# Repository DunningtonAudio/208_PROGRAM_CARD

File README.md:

# 208_PROGRAM_CARD
A 208 program card project

These Model 208 Program Cards are designed to interface with the “PROGRAM BOARD” edge connector of a Buchla & Associates Model 208 Stored Program Sound Source module and its reissues / compatible units. Two versions are provided, one for standard use and one with a prototyping area where additional active circuitry can be added if desired. For guidance on general use, see Allen Strange’s “Programming and Meta-Programming the Electro Organism” manual.

Beyond the settings / connections available on the original cards, the following features are provided:

* A label area on the rear of the card for easy identification of presets.
* Modulation oscillator range switch setting (where this is available on the 208 edge connector).
* An extra connection point for each of the random voltage outputs.
* Footprints for optional multi-turn trimmer potentiometers (Bourns 3266W type) in series with the sequencer voltage level settings for fine tune when programming pitched sequences.
* 5V rail brought out to the prototyping area (where this is available on the 208 edge connector)

Please read the notes before ordering or using cards.

The repository contains:

* KiCad project files, including gerber outputs
* Schematic, notes and 208 manual as PDF files

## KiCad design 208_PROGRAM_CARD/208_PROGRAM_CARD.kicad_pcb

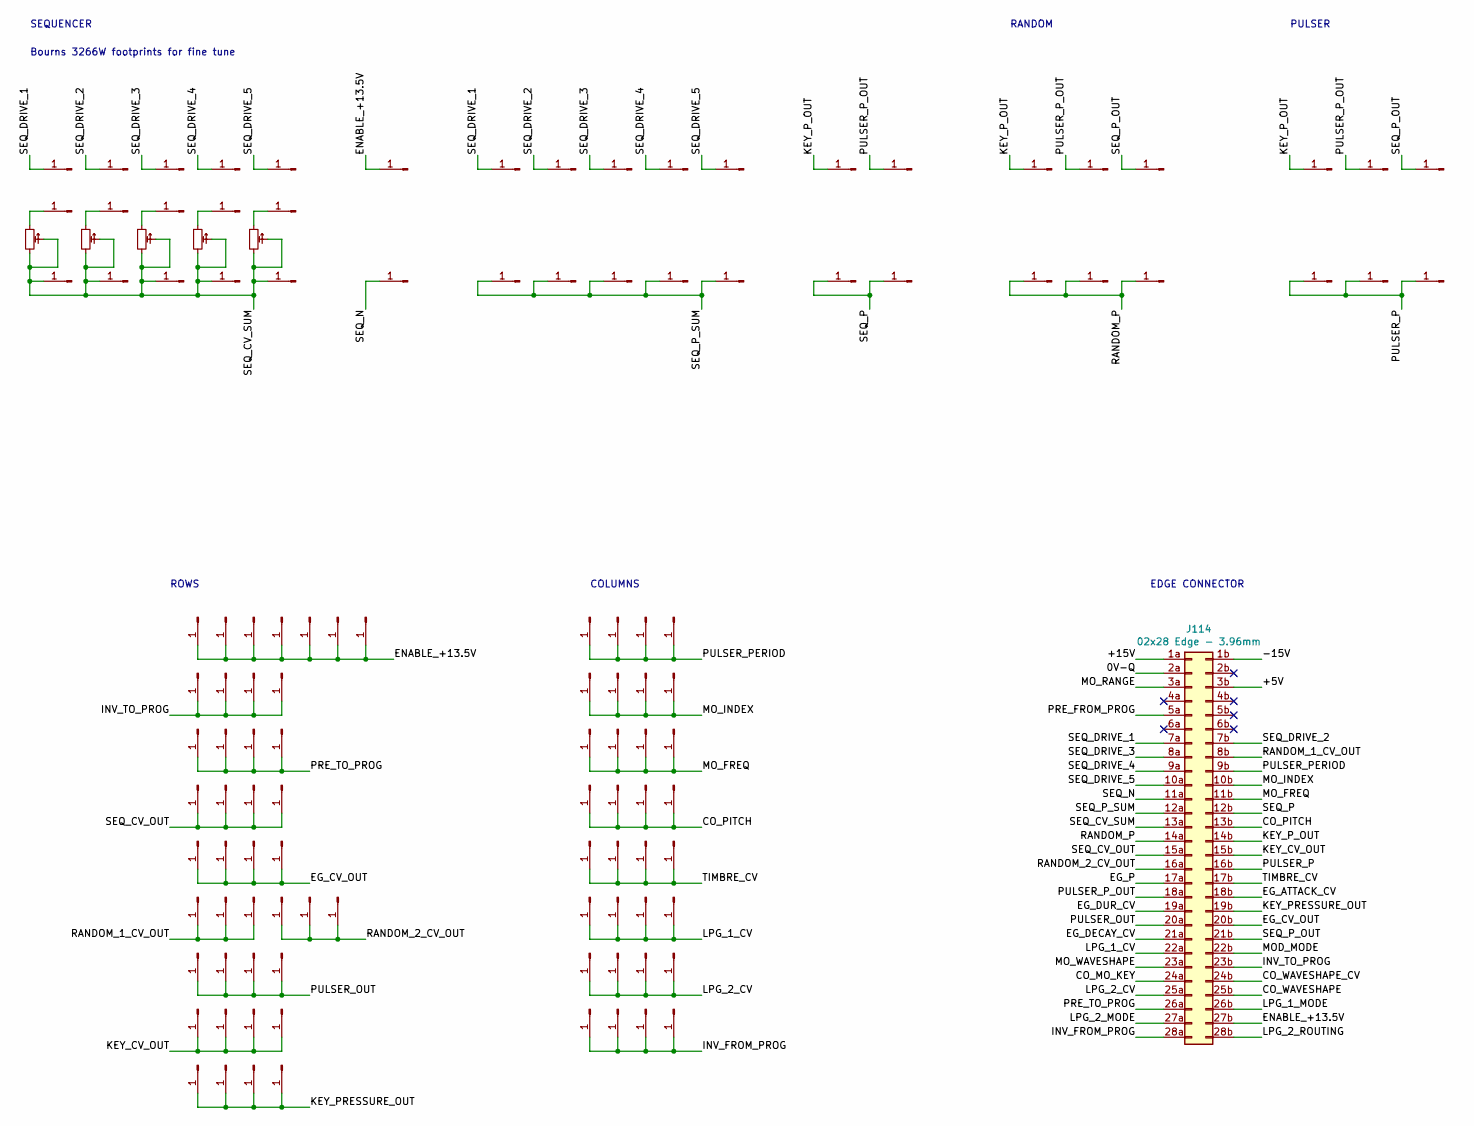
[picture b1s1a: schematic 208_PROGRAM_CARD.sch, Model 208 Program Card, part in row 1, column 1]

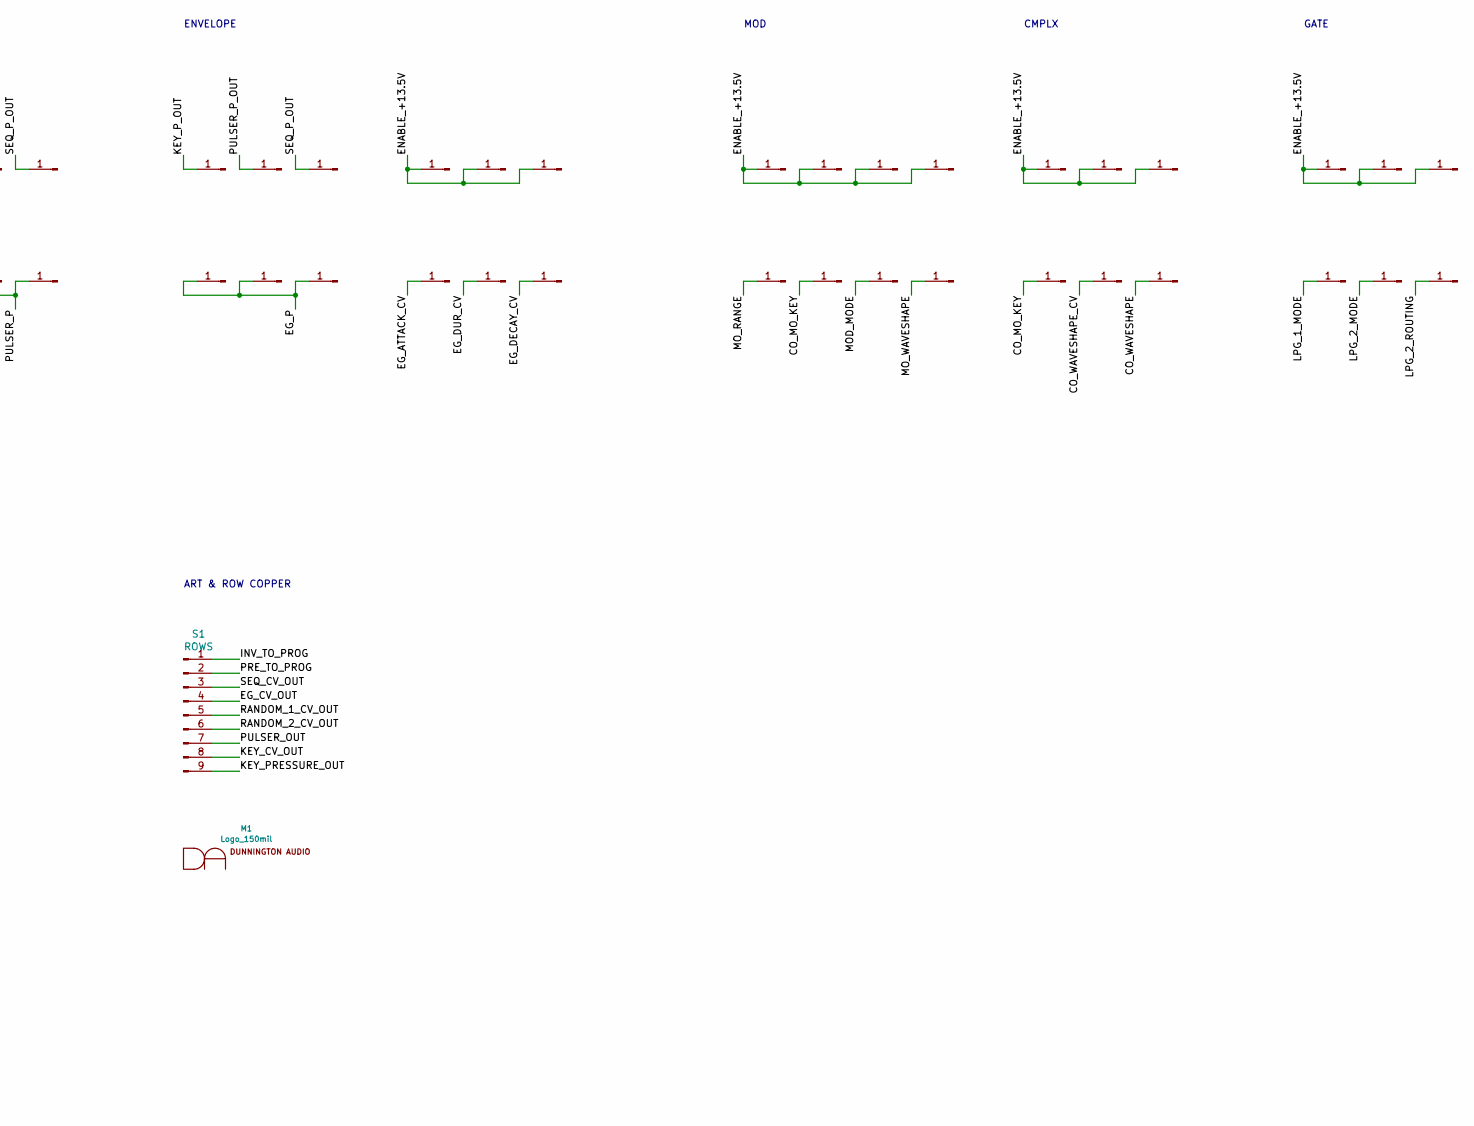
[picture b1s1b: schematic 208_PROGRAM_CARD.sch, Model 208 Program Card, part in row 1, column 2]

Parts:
J1, J2, J3, J4, J5, J6, J7, J8, J9, J10, J11, J12, J13, J14, J15, J16, J17, J18, J19, J20, J21, J22, J23, J24, J25, J26, J27, J28, J29, J30, J31, J32, J33, J34, J35, J36, J37, J38, J39, J40, J41, J42, J43, J44, J45, J46, J47, J48, J49, J50, J51, J52, J53, J54, J55, J56, J57, J58, J59, J60, J61, J62, J63, J64, J65, J66, J67, J68, J69, J70, J71, J72, J73, J74, J75, J76, J77, J78, J79, J80, J81, J82, J83, J84, J85, J86, J87, J88, J89, J90, J91, J92, J93, J94, J95, J96, J97, J98, J99, J100, J101, J102, J103, J104, J105, J106, J107, J108, J109, J110, J111, J112, J113, J115, J116, J117, J118, J119, J120, J121, J122, J123, J124, J125, J126, J127, J128, J129, J130, J131, J132, J133, J134, J135, J136, J137, J138, J139, J140, J141, J142, J143, J144, J354, J355, J356, J357, J358: Pad; SolderWirePad_1x01_Drill0.9mm
J114: 02x28 Edge - 3.96mm; 305-056-500-502_Mating_Edge
M1: Logo_150mil
S1: ROWS; 208_PROGRAM_CARD
TR1, TR2, TR3, TR4, TR5: TRIM; Potentiometer_Bourns_3266W_Vertical

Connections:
/0V-Q: J114.2a
/+5V: J114.3b
/+15V: J114.1a
/-15V: J114.1b
/CO_MO_KEY: J62.1, J65.1, J114.24a
/CO_PITCH: J102.1, J103.1, J104.1, J105.1, J114.13b
/CO_WAVESHAPE: J67.1, J114.25b
/CO_WAVESHAPE_CV: J66.1, J114.24b
/EG_ATTACK_CV: J58.1, J114.18b
/EG_CV_OUT: J106.1, J107.1, J108.1, J109.1, J114.20b, S1.4
/EG_DECAY_CV: J60.1, J114.21a
/EG_DUR_CV: J59.1, J114.19a
/EG_P: J55.1, J56.1, J57.1, J114.17a
/ENABLE_+13.5V: J6.1, J23.1, J24.1, J25.1, J26.1, J27.1, J28.1, J29.1, J30.1, J31.1, J32.1, J33.1, J34.1, J35.1, J71.1, J72.1, J73.1, J74.1, J75.1, J76.1, J77.1, J114.27b
/INV_FROM_PROG: J114.28a, J137.1, J138.1, J139.1, J140.1
/INV_TO_PROG: J82.1, J83.1, J84.1, J85.1, J114.23b, S1.1
/KEY_CV_OUT: J114.15b, J133.1, J134.1, J135.1, J136.1, S1.8
/KEY_PRESSURE_OUT: J114.19b, J141.1, J142.1, J143.1, J144.1, S1.9
/KEY_P_OUT: J12.1, J14.1, J17.1, J20.1, J114.14b
/LPG_1_CV: J114.22a, J121.1, J122.1, J123.1, J124.1
/LPG_1_MODE: J68.1, J114.26b
/LPG_2_CV: J114.25a, J129.1, J130.1, J131.1, J132.1
/LPG_2_MODE: J69.1, J114.27a
/LPG_2_ROUTING: J70.1, J114.28b
/MOD_MODE: J63.1, J114.22b
/MO_FREQ: J94.1, J95.1, J96.1, J97.1, J114.11b
/MO_INDEX: J86.1, J87.1, J88.1, J89.1, J114.10b
/MO_RANGE: J61.1, J114.3a
/MO_WAVESHAPE: J64.1, J114.23a
/PRE_FROM_PROG: J114.5a
/PRE_TO_PROG: J90.1, J91.1, J92.1, J93.1, J114.26a, S1.2
/PULSER_OUT: J114.20a, J125.1, J126.1, J127.1, J128.1, S1.7
/PULSER_P: J52.1, J53.1, J54.1, J114.16b
/PULSER_PERIOD: J78.1, J79.1, J80.1, J81.1, J114.9b
/PULSER_P_OUT: J13.1, J15.1, J18.1, J21.1, J114.18a
/RANDOM_1_CV_OUT: J114.8b, J115.1, J116.1, J117.1, S1.5
/RANDOM_2_CV_OUT: J114.16a, J118.1, J119.1, J120.1, S1.6
/RANDOM_P: J49.1, J50.1, J51.1, J114.14a
/SEQ_CV_OUT: J98.1, J99.1, J100.1, J101.1, J114.15a, S1.3
/SEQ_CV_SUM: J36.1, J37.1, J38.1, J39.1, J40.1, J114.13a, TR1.1, TR1.2, TR2.1, TR2.2, TR3.1, TR3.2, TR4.1, TR4.2, TR5.1, TR5.2
/SEQ_DRIVE_1: J1.1, J7.1, J114.7a
/SEQ_DRIVE_2: J2.1, J8.1, J114.7b
/SEQ_DRIVE_3: J3.1, J9.1, J114.8a
/SEQ_DRIVE_4: J4.1, J10.1, J114.9a
/SEQ_DRIVE_5: J5.1, J11.1, J114.10a
/SEQ_N: J41.1, J114.11a
/SEQ_P: J47.1, J48.1, J114.12b
/SEQ_P_OUT: J16.1, J19.1, J22.1, J114.21b
/SEQ_P_SUM: J42.1, J43.1, J44.1, J45.1, J46.1, J114.12a
/TIMBRE_CV: J110.1, J111.1, J112.1, J113.1, J114.17b
unnamed: J354.1, TR1.3
unnamed: J355.1, TR2.3
unnamed: J356.1, TR3.3
unnamed: J357.1, TR4.3
unnamed: J358.1, TR5.3

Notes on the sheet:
ROWS
COLUMNS
EDGE CONNECTOR
SEQUENCER
RANDOM
PULSER
ENVELOPE
MOD
CMPLX
GATE
ART & ROW COPPER
Bourns 3266W footprints for fine tune

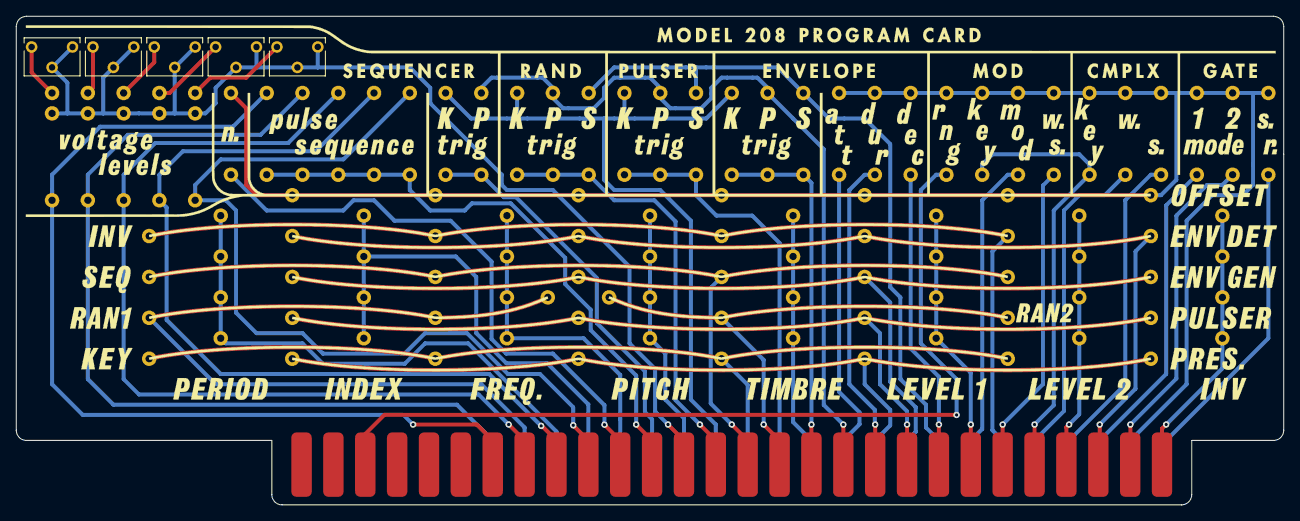
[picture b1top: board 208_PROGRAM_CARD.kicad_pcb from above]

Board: 2 copper layers, 157.5 x 60.7 mm, 156 parts (1 on the bottom side), 50 nets.

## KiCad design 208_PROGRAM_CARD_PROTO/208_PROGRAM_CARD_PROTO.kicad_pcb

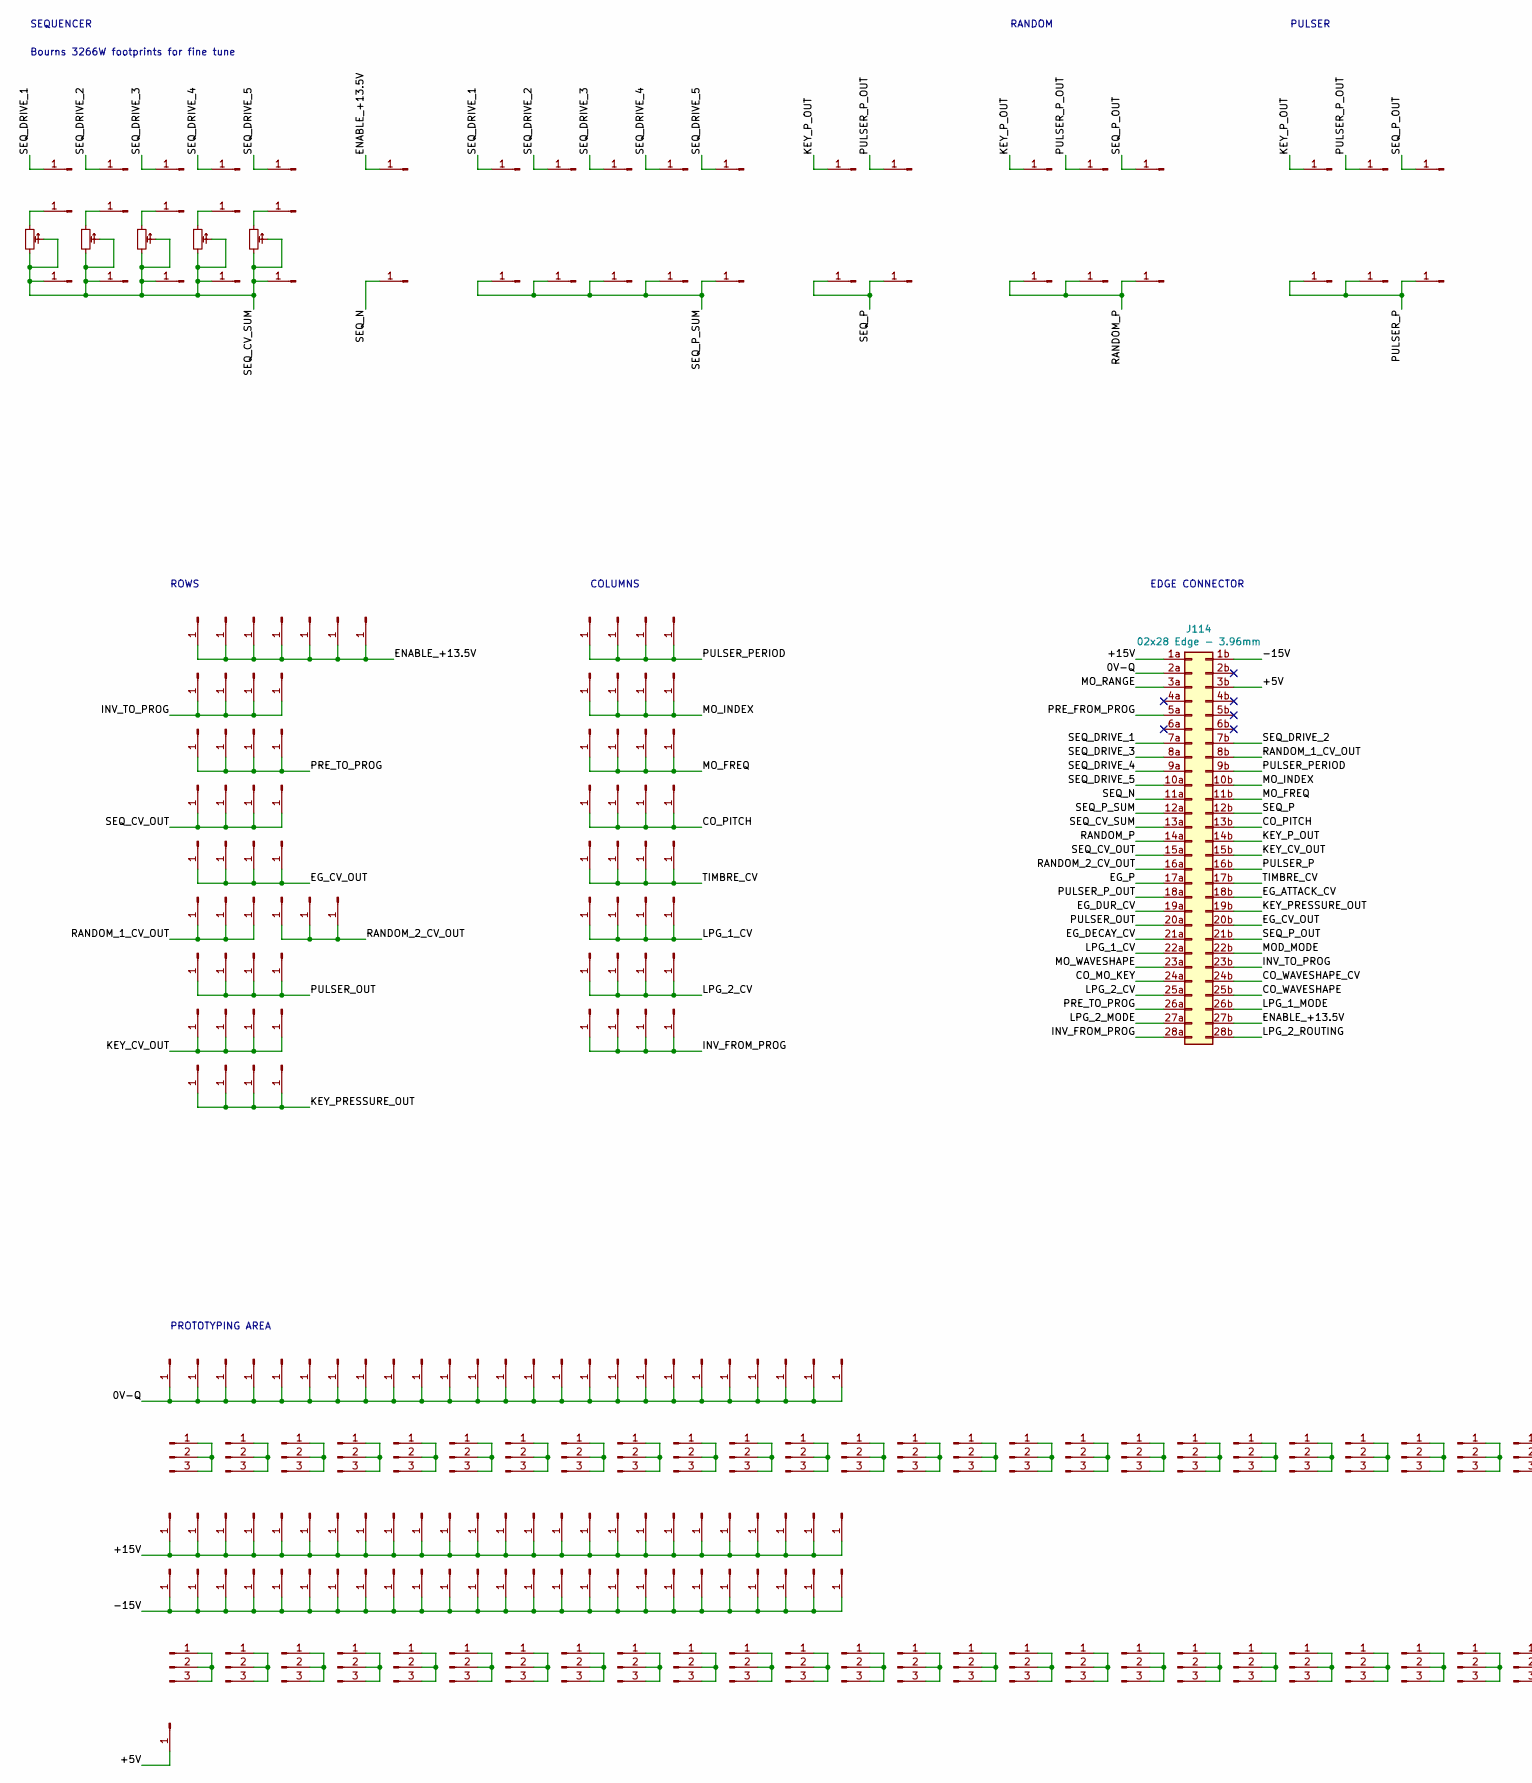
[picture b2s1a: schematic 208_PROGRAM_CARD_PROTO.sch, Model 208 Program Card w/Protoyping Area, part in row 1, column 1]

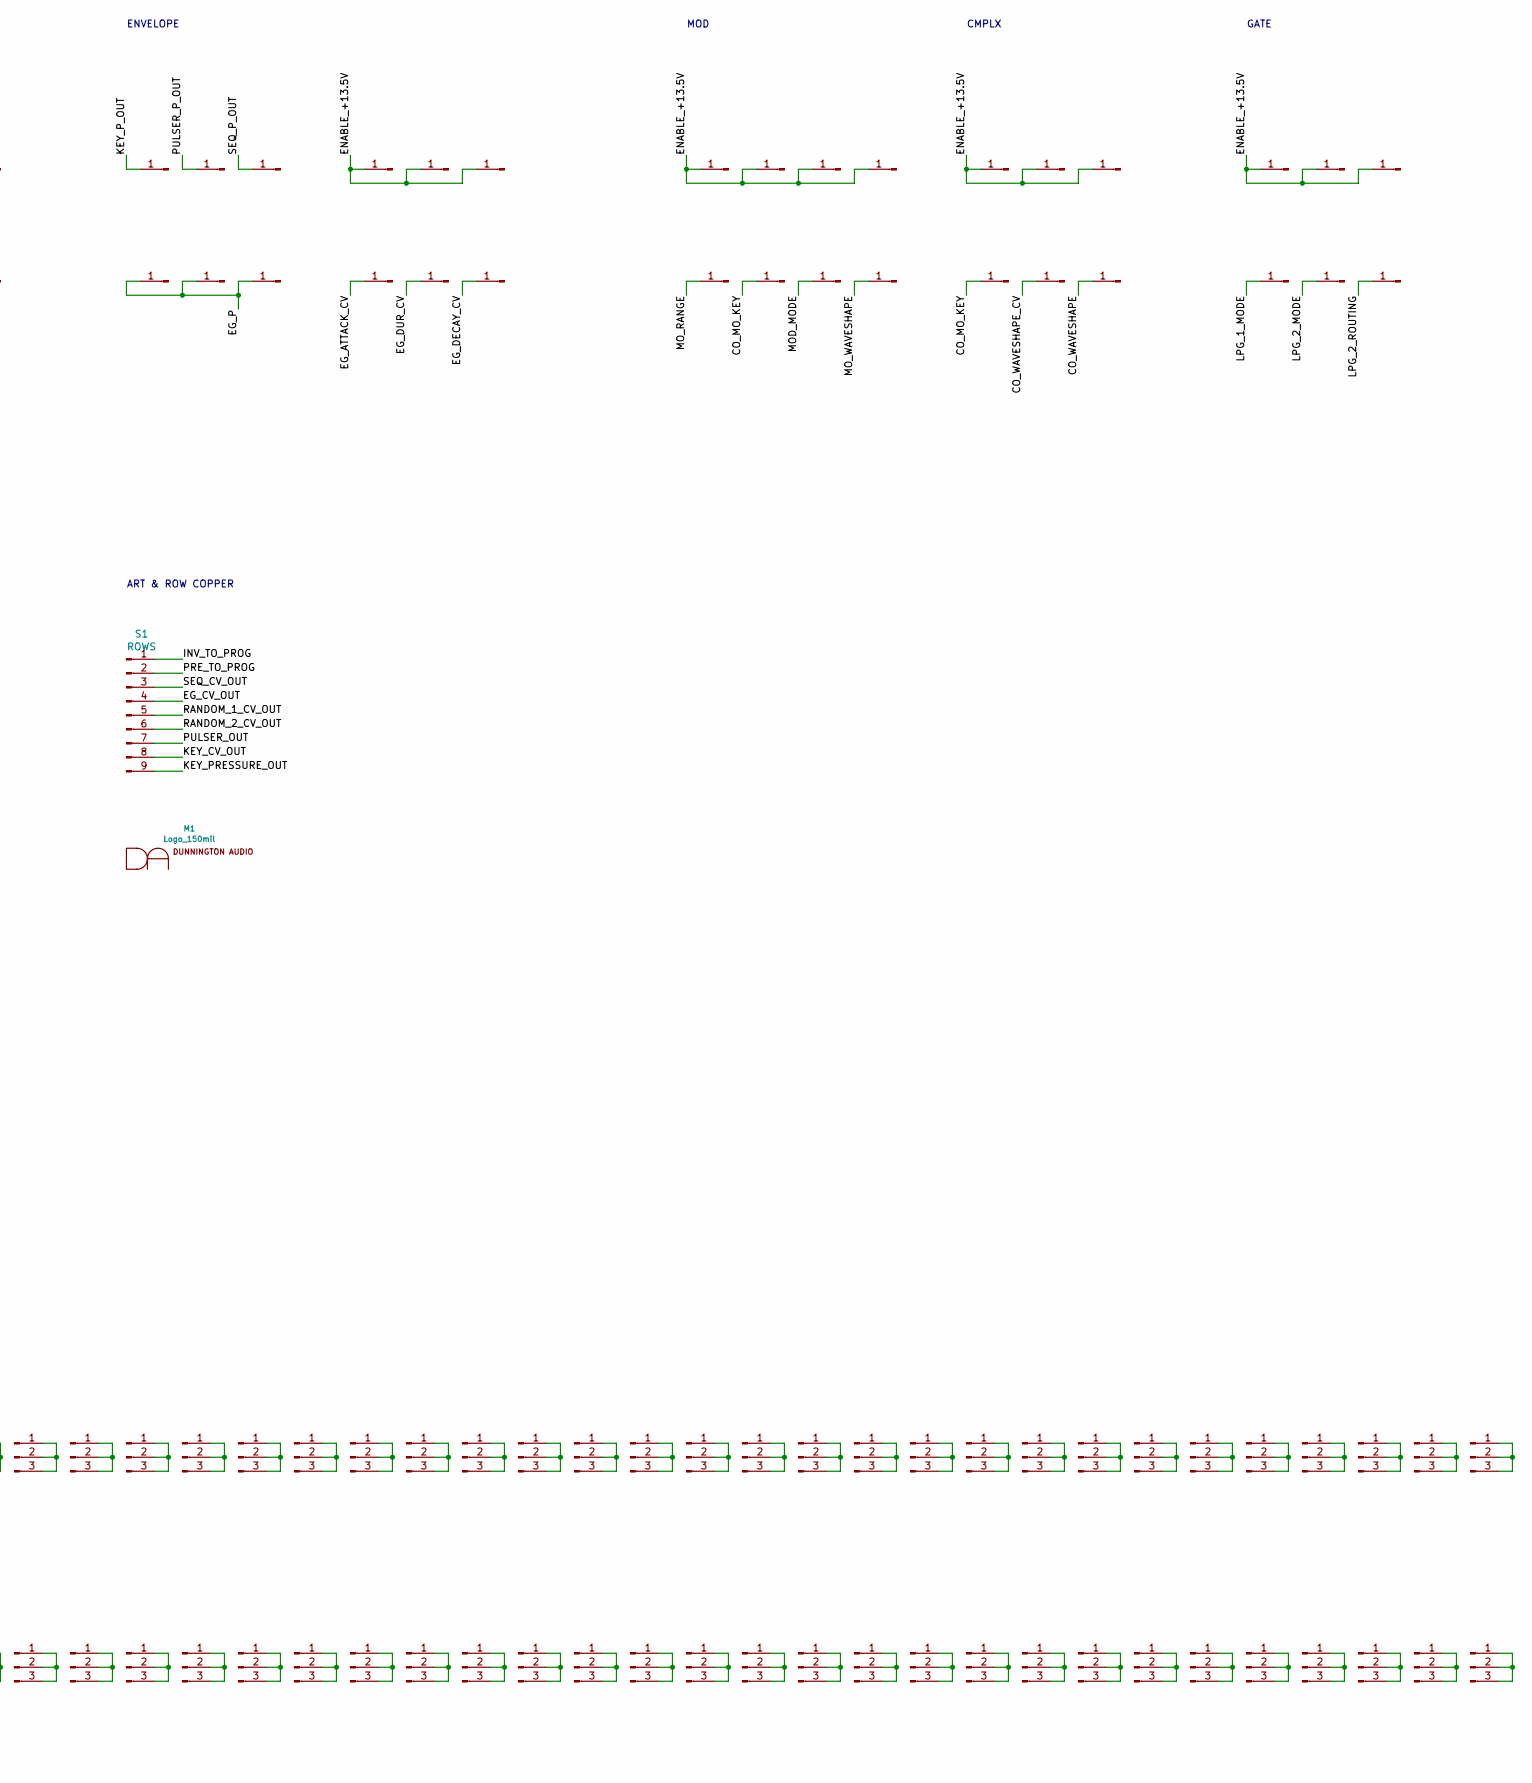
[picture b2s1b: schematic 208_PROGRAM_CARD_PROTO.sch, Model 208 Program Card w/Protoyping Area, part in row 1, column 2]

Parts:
J1, J2, J3, J4, J5, J6, J7, J8, J9, J10, J11, J12, J13, J14, J15, J16, J17, J18, J19, J20, J21, J22, J23, J24, J25, J26, J27, J28, J29, J30, J31, J32, J33, J34, J35, J36, J37, J38, J39, J40, J41, J42, J43, J44, J45, J46, J47, J48, J49, J50, J51, J52, J53, J54, J55, J56, J57, J58, J59, J60, J61, J62, J63, J64, J65, J66, J67, J68, J69, J70, J71, J72, J73, J74, J75, J76, J77, J78, J79, J80, J81, J82, J83, J84, J85, J86, J87, J88, J89, J90, J91, J92, J93, J94, J95, J96, J97, J98, J99, J100, J101, J102, J103, J104, J105, J106, J107, J108, J109, J110, J111, J112, J113, J115, J116, J117, J118, J119, J120, J121, J122, J123, J124, J125, J126, J127, J128, J129, J130, J131, J132, J133, J134, J135, J136, J137, J138, J139, J140, J141, J142, J143, J144, J145, J146, J147, J148, J149, J150, J151, J152, J153, J154, J155, J156, J157, J158, J159, J160, J161, J162, J163, J164, J165, J166, J167, J168, J169, J233, J234, J235, J236, J237, J238, J239, J240, J241, J242, J243, J244, J245, J246, J247, J248, J249, J250, J251, J252, J253, J254, J255, J256, J257, J265, J266, J267, J268, J269, J270, J271, J272, J273, J274, J275, J276, J277, J278, J279, J280, J281, J282, J283, J284, J285, J286, J287, J288, J289, J353, J354, J355, J356, J357, J358: Pad; SolderWirePad_1x01_Drill0.9mm
J114: 02x28 Edge - 3.96mm; 305-056-500-502_Mating_Edge
J177, J178, J179, J180, J181, J182, J183, J184, J185, J186, J187, J188, J189, J190, J191, J192, J193, J194, J195, J196, J197, J198, J199, J200, J201, J202, J203, J204, J205, J206, J207, J208, J209, J210, J211, J212, J213, J214, J215, J216, J217, J218, J219, J220, J221, J222, J223, J224, J225, J226, J297, J298, J299, J300, J301, J302, J303, J304, J305, J306, J307, J308, J309, J310, J311, J312, J313, J314, J315, J316, J317, J318, J319, J320, J321, J322, J323, J324, J325, J326, J327, J328, J329, J330, J331, J332, J333, J334, J335, J336, J337, J338, J339, J340, J341, J342, J343, J344, J345, J346: Muck Pads
M1: Logo_150mil
S1: ROWS; 208_PROGRAM_CARD_PROTO
TR1, TR2, TR3, TR4, TR5: TRIM; Potentiometer_Bourns_3266W_Vertical

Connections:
/0V-Q: J114.2a, J145.1, J146.1, J147.1, J148.1, J149.1, J150.1, J151.1, J152.1, J153.1, J154.1, J155.1, J156.1, J157.1, J158.1, J159.1, J160.1, J161.1, J162.1, J163.1, J164.1, J165.1, J166.1, J167.1, J168.1, J169.1
/+5V: J114.3b, J353.1
/+15V: J114.1a, J233.1, J234.1, J235.1, J236.1, J237.1, J238.1, J239.1, J240.1, J241.1, J242.1, J243.1, J244.1, J245.1, J246.1, J247.1, J248.1, J249.1, J250.1, J251.1, J252.1, J253.1, J254.1, J255.1, J256.1, J257.1
/-15V: J114.1b, J265.1, J266.1, J267.1, J268.1, J269.1, J270.1, J271.1, J272.1, J273.1, J274.1, J275.1, J276.1, J277.1, J278.1, J279.1, J280.1, J281.1, J282.1, J283.1, J284.1, J285.1, J286.1, J287.1, J288.1, J289.1
/CO_MO_KEY: J62.1, J65.1, J114.24a
/CO_PITCH: J102.1, J103.1, J104.1, J105.1, J114.13b
/CO_WAVESHAPE: J67.1, J114.25b
/CO_WAVESHAPE_CV: J66.1, J114.24b
/EG_ATTACK_CV: J58.1, J114.18b
/EG_CV_OUT: J106.1, J107.1, J108.1, J109.1, J114.20b, S1.4
/EG_DECAY_CV: J60.1, J114.21a
/EG_DUR_CV: J59.1, J114.19a
/EG_P: J55.1, J56.1, J57.1, J114.17a
/ENABLE_+13.5V: J6.1, J23.1, J24.1, J25.1, J26.1, J27.1, J28.1, J29.1, J30.1, J31.1, J32.1, J33.1, J34.1, J35.1, J71.1, J72.1, J73.1, J74.1, J75.1, J76.1, J77.1, J114.27b
/INV_FROM_PROG: J114.28a, J137.1, J138.1, J139.1, J140.1
/INV_TO_PROG: J82.1, J83.1, J84.1, J85.1, J114.23b, S1.1
/KEY_CV_OUT: J114.15b, J133.1, J134.1, J135.1, J136.1, S1.8
/KEY_PRESSURE_OUT: J114.19b, J141.1, J142.1, J143.1, J144.1, S1.9
/KEY_P_OUT: J12.1, J14.1, J17.1, J20.1, J114.14b
/LPG_1_CV: J114.22a, J121.1, J122.1, J123.1, J124.1
/LPG_1_MODE: J68.1, J114.26b
/LPG_2_CV: J114.25a, J129.1, J130.1, J131.1, J132.1
/LPG_2_MODE: J69.1, J114.27a
/LPG_2_ROUTING: J70.1, J114.28b
/MOD_MODE: J63.1, J114.22b
/MO_FREQ: J94.1, J95.1, J96.1, J97.1, J114.11b
/MO_INDEX: J86.1, J87.1, J88.1, J89.1, J114.10b
/MO_RANGE: J61.1, J114.3a
/MO_WAVESHAPE: J64.1, J114.23a
/PRE_FROM_PROG: J114.5a
/PRE_TO_PROG: J90.1, J91.1, J92.1, J93.1, J114.26a, S1.2
/PULSER_OUT: J114.20a, J125.1, J126.1, J127.1, J128.1, S1.7
/PULSER_P: J52.1, J53.1, J54.1, J114.16b
/PULSER_PERIOD: J78.1, J79.1, J80.1, J81.1, J114.9b
/PULSER_P_OUT: J13.1, J15.1, J18.1, J21.1, J114.18a
/RANDOM_1_CV_OUT: J114.8b, J115.1, J116.1, J117.1, S1.5
/RANDOM_2_CV_OUT: J114.16a, J118.1, J119.1, J120.1, S1.6
/RANDOM_P: J49.1, J50.1, J51.1, J114.14a
/SEQ_CV_OUT: J98.1, J99.1, J100.1, J101.1, J114.15a, S1.3
/SEQ_CV_SUM: J36.1, J37.1, J38.1, J39.1, J40.1, J114.13a, TR1.1, TR1.2, TR2.1, TR2.2, TR3.1, TR3.2, TR4.1, TR4.2, TR5.1, TR5.2
/SEQ_DRIVE_1: J1.1, J7.1, J114.7a
/SEQ_DRIVE_2: J2.1, J8.1, J114.7b
/SEQ_DRIVE_3: J3.1, J9.1, J114.8a
/SEQ_DRIVE_4: J4.1, J10.1, J114.9a
/SEQ_DRIVE_5: J5.1, J11.1, J114.10a
/SEQ_N: J41.1, J114.11a
/SEQ_P: J47.1, J48.1, J114.12b
/SEQ_P_OUT: J16.1, J19.1, J22.1, J114.21b
/SEQ_P_SUM: J42.1, J43.1, J44.1, J45.1, J46.1, J114.12a
/TIMBRE_CV: J110.1, J111.1, J112.1, J113.1, J114.17b
unnamed: J177.1, J177.2, J177.3
unnamed: J178.1, J178.2, J178.3
unnamed: J179.1, J179.2, J179.3
unnamed: J180.1, J180.2, J180.3
unnamed: J181.1, J181.2, J181.3
unnamed: J182.1, J182.2, J182.3
unnamed: J183.1, J183.2, J183.3
unnamed: J184.1, J184.2, J184.3
unnamed: J185.1, J185.2, J185.3
unnamed: J186.1, J186.2, J186.3
unnamed: J187.1, J187.2, J187.3
unnamed: J188.1, J188.2, J188.3
unnamed: J189.1, J189.2, J189.3
unnamed: J190.1, J190.2, J190.3
unnamed: J191.1, J191.2, J191.3
unnamed: J192.1, J192.2, J192.3
unnamed: J193.1, J193.2, J193.3
unnamed: J194.1, J194.2, J194.3
unnamed: J195.1, J195.2, J195.3
unnamed: J196.1, J196.2, J196.3
unnamed: J197.1, J197.2, J197.3
unnamed: J198.1, J198.2, J198.3
unnamed: J199.1, J199.2, J199.3
unnamed: J200.1, J200.2, J200.3
unnamed: J201.1, J201.2, J201.3
unnamed: J202.1, J202.2, J202.3
unnamed: J203.1, J203.2, J203.3
unnamed: J204.1, J204.2, J204.3
unnamed: J205.1, J205.2, J205.3
unnamed: J206.1, J206.2, J206.3
unnamed: J207.1, J207.2, J207.3
unnamed: J208.1, J208.2, J208.3
unnamed: J209.1, J209.2, J209.3
unnamed: J210.1, J210.2, J210.3
unnamed: J211.1, J211.2, J211.3
unnamed: J212.1, J212.2, J212.3
unnamed: J213.1, J213.2, J213.3
unnamed: J214.1, J214.2, J214.3
unnamed: J215.1, J215.2, J215.3
unnamed: J216.1, J216.2, J216.3
unnamed: J217.1, J217.2, J217.3
unnamed: J218.1, J218.2, J218.3
unnamed: J219.1, J219.2, J219.3
unnamed: J220.1, J220.2, J220.3
unnamed: J221.1, J221.2, J221.3
unnamed: J222.1, J222.2, J222.3
unnamed: J223.1, J223.2, J223.3
unnamed: J224.1, J224.2, J224.3
unnamed: J225.1, J225.2, J225.3
unnamed: J226.1, J226.2, J226.3
unnamed: J297.1, J297.2, J297.3
unnamed: J298.1, J298.2, J298.3
unnamed: J299.1, J299.2, J299.3
unnamed: J300.1, J300.2, J300.3
unnamed: J301.1, J301.2, J301.3
unnamed: J302.1, J302.2, J302.3
unnamed: J303.1, J303.2, J303.3
unnamed: J304.1, J304.2, J304.3
unnamed: J305.1, J305.2, J305.3
unnamed: J306.1, J306.2, J306.3
unnamed: J307.1, J307.2, J307.3
unnamed: J308.1, J308.2, J308.3
unnamed: J309.1, J309.2, J309.3
unnamed: J310.1, J310.2, J310.3
unnamed: J311.1, J311.2, J311.3
unnamed: J312.1, J312.2, J312.3
unnamed: J313.1, J313.2, J313.3
unnamed: J314.1, J314.2, J314.3
unnamed: J315.1, J315.2, J315.3
unnamed: J316.1, J316.2, J316.3
unnamed: J317.1, J317.2, J317.3
unnamed: J318.1, J318.2, J318.3
unnamed: J319.1, J319.2, J319.3
unnamed: J320.1, J320.2, J320.3
unnamed: J321.1, J321.2, J321.3
unnamed: J322.1, J322.2, J322.3
unnamed: J323.1, J323.2, J323.3
unnamed: J324.1, J324.2, J324.3
unnamed: J325.1, J325.2, J325.3
unnamed: J326.1, J326.2, J326.3
unnamed: J327.1, J327.2, J327.3
unnamed: J328.1, J328.2, J328.3
unnamed: J329.1, J329.2, J329.3
unnamed: J330.1, J330.2, J330.3
unnamed: J331.1, J331.2, J331.3
unnamed: J332.1, J332.2, J332.3
unnamed: J333.1, J333.2, J333.3
unnamed: J334.1, J334.2, J334.3
unnamed: J335.1, J335.2, J335.3
unnamed: J336.1, J336.2, J336.3
unnamed: J337.1, J337.2, J337.3
unnamed: J338.1, J338.2, J338.3
unnamed: J339.1, J339.2, J339.3
unnamed: J340.1, J340.2, J340.3
unnamed: J341.1, J341.2, J341.3
unnamed: J342.1, J342.2, J342.3
unnamed: J343.1, J343.2, J343.3
unnamed: J344.1, J344.2, J344.3
unnamed: J345.1, J345.2, J345.3
unnamed: J346.1, J346.2, J346.3
unnamed: J354.1, TR1.3
unnamed: J355.1, TR2.3
unnamed: J356.1, TR3.3
unnamed: J357.1, TR4.3
unnamed: J358.1, TR5.3

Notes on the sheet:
ROWS
COLUMNS
EDGE CONNECTOR
SEQUENCER
RANDOM
PULSER
ENVELOPE
MOD
CMPLX
GATE
ART & ROW COPPER
Bourns 3266W footprints for fine tune
PROTOTYPING AREA

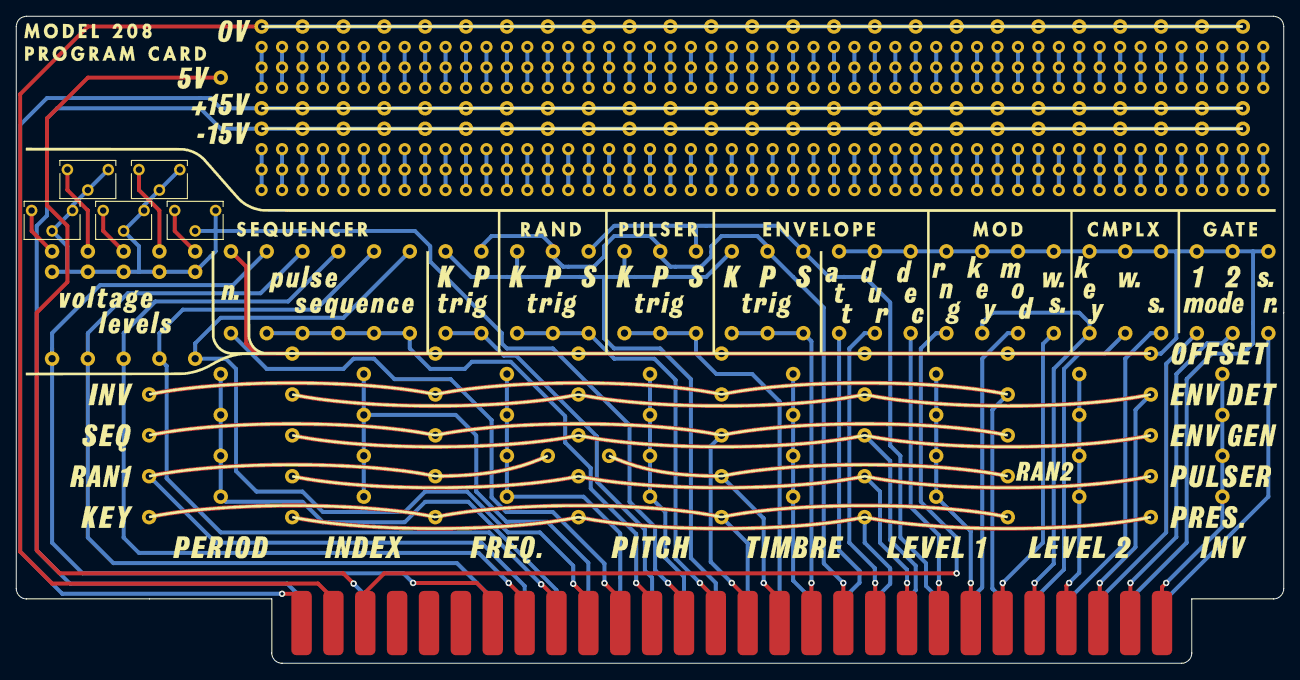
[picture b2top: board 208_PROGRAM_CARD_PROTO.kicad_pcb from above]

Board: 2 copper layers, 157.5 x 80.4 mm, 332 parts (1 on the bottom side), 154 nets.

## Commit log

2021-05-11 Add license & readme
2021-05-11 Readme update
